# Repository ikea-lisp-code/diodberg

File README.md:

# diodberg

diodberg runs new experimental climbing wall from 'ikea-lisp-code.

The python diodberg module is currently **DEPRECATED**. Development on the wall
client software has moved to a fork of [Firemix]
(https://github.com/ikea-lisp-code/firemix).

If you are currently working on the wall, I recommend just checking out the
repository directly and using classes through the directory hierarchy instead
of using the setup.py file.

Directory/package contents in python/diodberg/:
* core

  Basic types, runner, and rendering objects. User applications interact with
  the wall by directly manipulating pixels on a Panel through an iterator
  interface. This is a strong candidate for future performance improvements.

* data 
  
  Sample configuration files. 

* input
  
  Nothing here! Currently, we lack both software and hardware support for
  sensor input to the wall while in-flight.

* user_plugins

  User applications for running visualizations. If you are writing an
  application to run on the wall, check out things here.

* renderers

  Simulation, serial, and GPIO interfaces for driving lights.

* util

  Misc.: random utilities

* web
  
  A Flask-based web front-end for configuring, controlling, and running lights.

...and: 
* docs
* firmware

  Device firmware for DMX intermediaries

* schematics

# Package requirements
* Python 2.7 
* numpy/scipy
* If simulating plugins: Pygame
* If running serial protocols: pyserial and RPi
* If running the web front end: Flask.
* If using performance optimizations: Numba (and by extension, the Anaconda
  Python distribution). 
* If using audio input: aubio (and its many dependencies).

# Installation and setup instructions
  
  TODO (see above)

# Questions? 

Email <mookerji@spin-one.org>, <chris@notspelledright.com>, <yuanyu.chen@gmail.com>

# License

Copyright (C) 2013 ikea-lisp-code. Distributed under the MIT License.

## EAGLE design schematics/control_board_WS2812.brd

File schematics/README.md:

# diodberg schematics

diodberg schematics require Eagle v6.3.0 or later

...filenames will be cleaned up soon...

# Questions? 

Email <chris@notspelledright.com>, <yuanyu.chen@gmail.com>

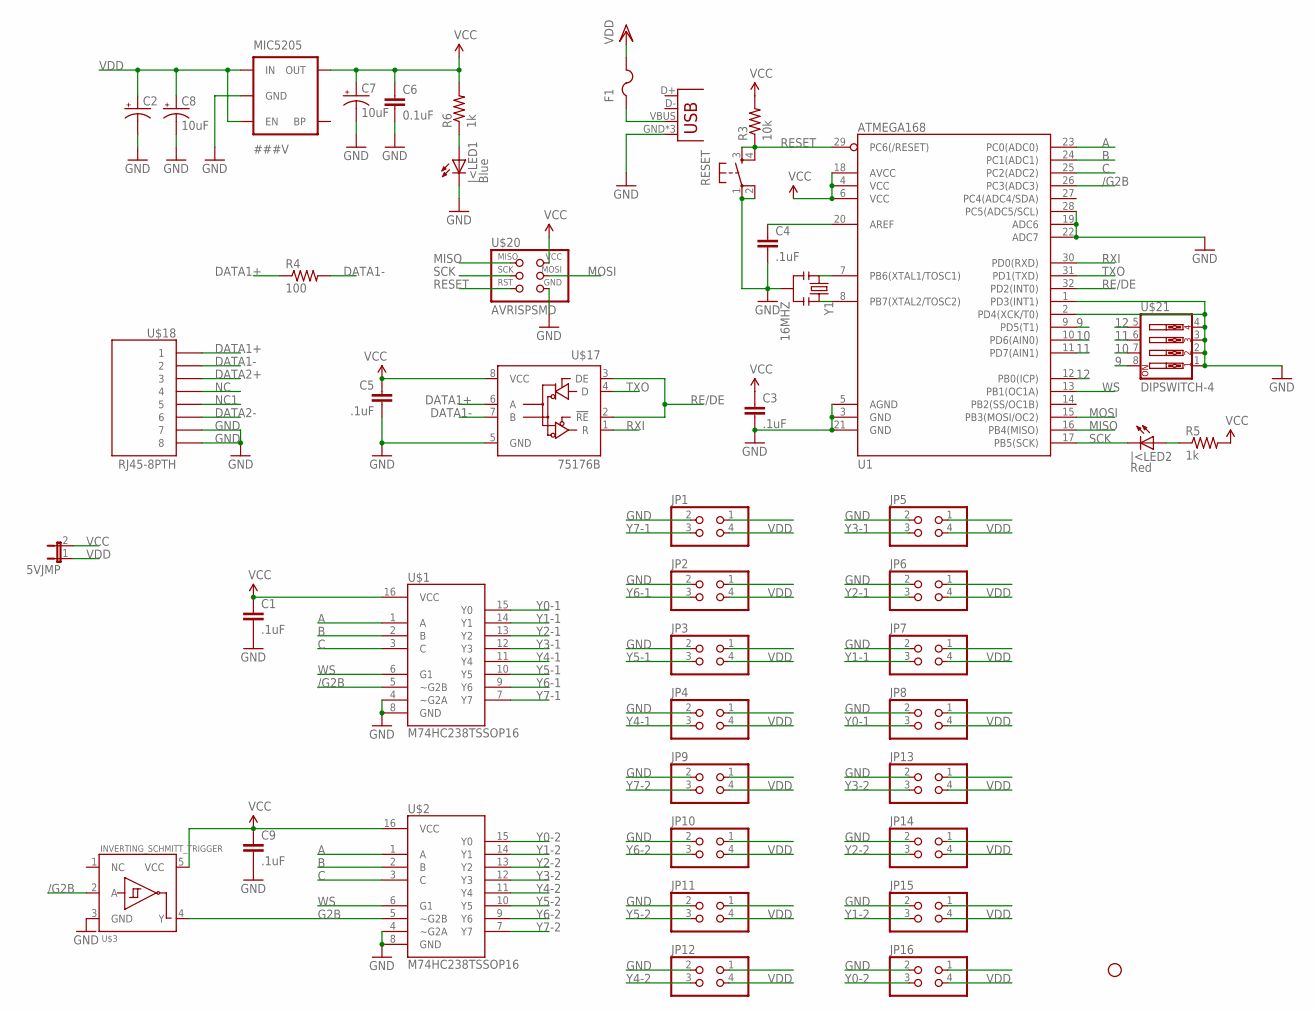
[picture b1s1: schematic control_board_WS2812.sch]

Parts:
5VJMP: JUMPER-2SMD-NO; SJ_2S-NO
C1, C3, C4, C5, C9: .1uF; 0402-CAP
C2: CAP_POLC; PANASONIC_C
C6: 0.1uF; 0402-CAP
C7, C8: 10uF; EIA3216
F1: PTCFUSE-1812; 1812
JP1, JP2, JP3, JP4, JP5, JP6, JP7, JP8, JP9, JP10, JP11, JP12, JP13, JP14, JP15, JP16: PINHD-2X2; 2X02
JP17: USB-MICROB
MIC5205: ###V; SOT23-5
R3: 10k; 0402-RES
R4: 100; 1206
R5, R6: 1k; C0402
RESET: TAC_SWITCHSMD; TACTILE_SWITCH_SMD
STANDOFF1: STAND-OFF
U1: ATMEGA168; TQFP32-08
U$1, U$2: M74HC238TSSOP16; TSSOP16
U$3: INVERTING_SCHMITT_TRIGGER; TSSOP5
U$17: 75176B; D_R-PDSO-G8
U$18: RJ45-8PTH; RJ45-8
U$20: AVRISPSMD; 2X03SMD
U$21: DIPSWITCH-4; DIPSWITCH-04
Y1: 16MHZ; RESONATOR-SMD
|<LED1: Blue; LED-0603
|<LED2: Red; LED-0603

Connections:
9: U1.9 (PD5(T1)), U$21.8
10: U1.10 (PD6(AIN0)), U$21.7
11: U1.11 (PD7(AIN1)), U$21.6
12: U1.12 (PB0(ICP)), U$21.5
/G2B: U1.26 (PC3(ADC3)), U$1.5 (~G2B), U$3.2 (A)
A: U1.23 (PC0(ADC0)), U$1.1 (A), U$2.1 (A)
B: U1.24 (PC1(ADC1)), U$1.2 (B), U$2.2 (B)
C: U1.25 (PC2(ADC2)), U$1.3 (C), U$2.3 (C)
DATA1+: R4.1, U$17.6 (A), U$18.1
DATA1-: R4.2, U$17.7 (B), U$18.2
DATA2+: U$18.3
DATA2-: U$18.6
G2B: U$2.5 (~G2B), U$3.4 (Y)
GND: C1.2, C2.-, C3.2, C4.2, C5.2, C6.2, C7.C (-), C8.C (-), C9.2, JP1.2, JP2.2, JP3.2, JP4.2, JP5.2, JP6.2, JP7.2, JP8.2, JP9.2, JP10.2, JP11.2, JP12.2, JP13.2, JP14.2, JP15.2, JP16.2, JP17.GND, JP17.MT1 (GND), JP17.MT2 (GND), MIC5205.2 (GND), RESET.1, RESET.2, U1.1 (PD3(INT1)), U1.2 (PD4(XCK/T0)), U1.3 (GND), U1.5 (AGND), U1.19 (ADC6), U1.21 (GND), U1.22 (ADC7), U1.28 (PC5(ADC5/SCL)), U$1.4 (~G2A), U$1.8 (GND), U$2.4 (~G2A), U$2.8 (GND), U$3.3 (GND), U$17.5 (GND), U$18.7, U$18.8, U$20.6 (GND), U$21.1, U$21.2, U$21.3, U$21.4, Y1.2, |<LED1.C
MISO: U1.16 (PB4(MISO)), U$20.1 (MISO)
MOSI: U1.15 (PB3(MOSI/OC2)), U$20.4 (MOSI)
unnamed: C4.1, U1.20 (AREF)
unnamed: U1.7 (PB6(XTAL1/TOSC1)), Y1.1
unnamed: U1.8 (PB7(XTAL2/TOSC2)), Y1.3
unnamed: R5.1, |<LED2.A
unnamed: F1.1, JP17.VBUS
unnamed: R6.1, |<LED1.A
NC: U$18.4
NC1: U$18.5
RE/DE: U1.32 (PD2(INT0)), U$17.2 (!RE), U$17.3 (DE)
RESET: R3.1, RESET.3, RESET.4, U1.29 (PC6(/RESET)), U$20.5 (RST)
RXI: U1.30 (PD0(RXD)), U$17.1 (R)
SCK: U1.17 (PB5(SCK)), U$20.3 (SCK), |<LED2.C
TXO: U1.31 (PD1(TXD)), U$17.4 (D)
VCC: 5VJMP.2, C1.1, C3.1, C5.1, C6.1, C7.A (+), C9.1, MIC5205.5 (OUT), R3.2, R5.2, R6.2, U1.4 (VCC), U1.6 (VCC), U1.18 (AVCC), U$1.16 (VCC), U$2.16 (VCC), U$3.5 (VCC), U$17.8 (VCC), U$20.2 (VCC)
VDD: 5VJMP.1, C2.+, C8.A (+), F1.2, JP1.4, JP2.4, JP3.4, JP4.4, JP5.4, JP6.4, JP7.4, JP8.4, JP9.4, JP10.4, JP11.4, JP12.4, JP13.4, JP14.4, JP15.4, JP16.4, MIC5205.1 (IN), MIC5205.3 (EN)
WS: U1.13 (PB1(OC1A)), U$1.6 (G1), U$2.6 (G1)
Y0-1: JP8.3, U$1.15 (Y0)
Y0-2: JP16.3, U$2.15 (Y0)
Y1-1: JP7.3, U$1.14 (Y1)
Y1-2: JP15.3, U$2.14 (Y1)
Y2-1: JP6.3, U$1.13 (Y2)
Y2-2: JP14.3, U$2.13 (Y2)
Y3-1: JP5.3, U$1.12 (Y3)
Y3-2: JP13.3, U$2.12 (Y3)
Y4-1: JP4.3, U$1.11 (Y4)
Y4-2: JP12.3, U$2.11 (Y4)
Y5-1: JP3.3, U$1.10 (Y5)
Y5-2: JP11.3, U$2.10 (Y5)
Y6-1: JP2.3, U$1.9 (Y6)
Y6-2: JP10.3, U$2.9 (Y6)
Y7-1: JP1.3, U$1.7 (Y7)
Y7-2: JP9.3, U$2.7 (Y7)

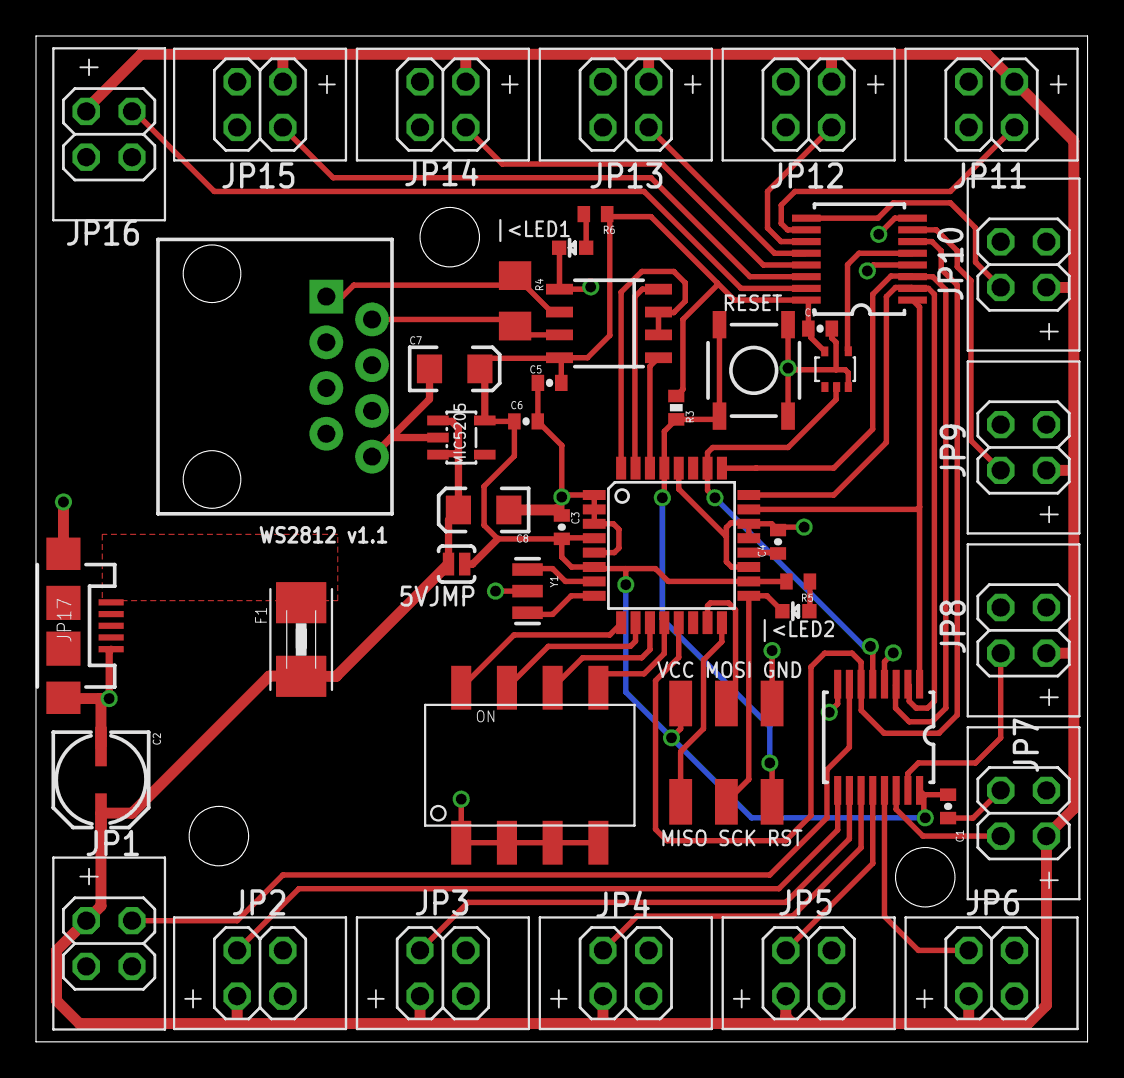
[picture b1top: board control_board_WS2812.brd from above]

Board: 2 copper layers, 58.4 x 55.9 mm, 48 parts (0 on the bottom side), 44 nets.

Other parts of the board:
STANDOFF2, STANDOFF3: STAND-OFF

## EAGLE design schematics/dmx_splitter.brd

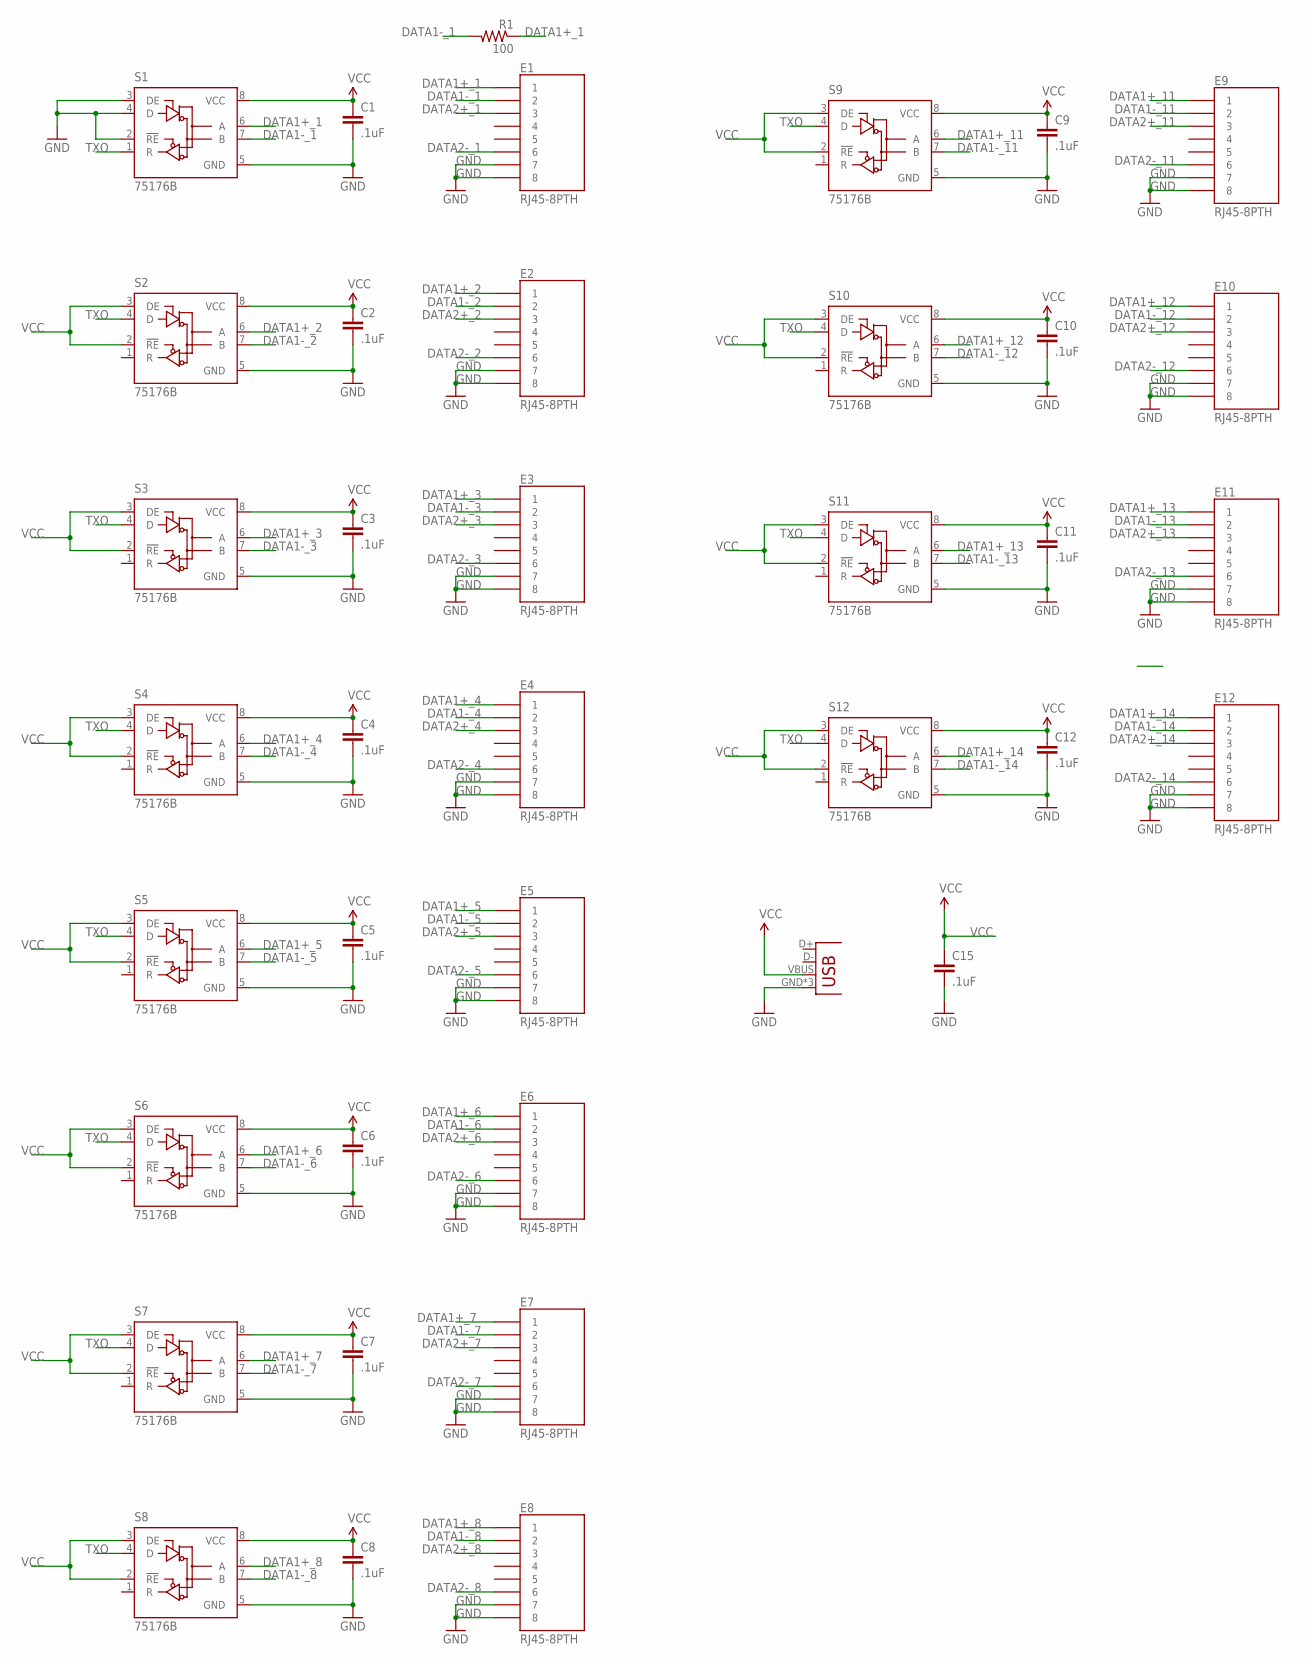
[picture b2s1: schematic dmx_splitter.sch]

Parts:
C1, C2, C3, C4, C5, C6, C7, C8, C9, C10, C11, C12, C15: .1uF; 0402-CAP
E1, E2, E3, E4, E5, E6, E7, E8, E9, E10, E11, E12: RJ45-8PTH; RJ45-8
JP1: USB-MICROB
R1: 100; 1206
S1, S2, S3, S4, S5, S6, S7, S8, S9, S10, S11, S12: 75176B; D_R-PDSO-G8

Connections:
DATA1+_1: E1.1, R1.1, S1.6 (A)
DATA1+_2: E2.1, S2.6 (A)
DATA1+_3: E3.1, S3.6 (A)
DATA1+_4: E4.1, S4.6 (A)
DATA1+_5: E5.1, S5.6 (A)
DATA1+_6: E6.1, S6.6 (A)
DATA1+_7: E7.1, S7.6 (A)
DATA1+_8: E8.1, S8.6 (A)
DATA1+_11: E9.1, S9.6 (A)
DATA1+_12: E10.1, S10.6 (A)
DATA1+_13: E11.1, S11.6 (A)
DATA1+_14: E12.1, S12.6 (A)
DATA1-_1: E1.2, R1.2, S1.7 (B)
DATA1-_2: E2.2, S2.7 (B)
DATA1-_3: E3.2, S3.7 (B)
DATA1-_4: E4.2, S4.7 (B)
DATA1-_5: E5.2, S5.7 (B)
DATA1-_6: E6.2, S6.7 (B)
DATA1-_7: E7.2, S7.7 (B)
DATA1-_8: E8.2, S8.7 (B)
DATA1-_11: E9.2, S9.7 (B)
DATA1-_12: E10.2, S10.7 (B)
DATA1-_13: E11.2, S11.7 (B)
DATA1-_14: E12.2, S12.7 (B)
DATA2+_1: E1.3
DATA2+_2: E2.3
DATA2+_3: E3.3
DATA2+_4: E4.3
DATA2+_5: E5.3
DATA2+_6: E6.3
DATA2+_7: E7.3
DATA2+_8: E8.3
DATA2+_11: E9.3
DATA2+_12: E10.3
DATA2+_13: E11.3
DATA2+_14: E12.3
DATA2-_1: E1.6
DATA2-_2: E2.6
DATA2-_3: E3.6
DATA2-_4: E4.6
DATA2-_5: E5.6
DATA2-_6: E6.6
DATA2-_7: E7.6
DATA2-_8: E8.6
DATA2-_11: E9.6
DATA2-_12: E10.6
DATA2-_13: E11.6
DATA2-_14: E12.6
GND: C1.2, C2.2, C3.2, C4.2, C5.2, C6.2, C7.2, C8.2, C9.2, C10.2, C11.2, C12.2, C15.2, E1.7, E1.8, E2.7, E2.8, E3.7, E3.8, E4.7, E4.8, E5.7, E5.8, E6.7, E6.8, E7.7, E7.8, E8.7, E8.8, E9.7, E9.8, E10.7, E10.8, E11.7, E11.8, E12.7, E12.8, JP1.GND, JP1.MT1 (GND), JP1.MT2 (GND), S1.2 (!RE), S1.3 (DE), S1.4 (D), S1.5 (GND), S2.5 (GND), S3.5 (GND), S4.5 (GND), S5.5 (GND), S6.5 (GND), S7.5 (GND), S8.5 (GND), S9.5 (GND), S10.5 (GND), S11.5 (GND), S12.5 (GND)
TXO: S1.1 (R), S2.4 (D), S3.4 (D), S4.4 (D), S5.4 (D), S6.4 (D), S7.4 (D), S8.4 (D), S9.4 (D), S10.4 (D), S11.4 (D), S12.4 (D)
VCC: C1.1, C2.1, C3.1, C4.1, C5.1, C6.1, C7.1, C8.1, C9.1, C10.1, C11.1, C12.1, C15.1, JP1.VBUS, S1.8 (VCC), S2.2 (!RE), S2.3 (DE), S2.8 (VCC), S3.2 (!RE), S3.3 (DE), S3.8 (VCC), S4.2 (!RE), S4.3 (DE), S4.8 (VCC), S5.2 (!RE), S5.3 (DE), S5.8 (VCC), S6.2 (!RE), S6.3 (DE), S6.8 (VCC), S7.2 (!RE), S7.3 (DE), S7.8 (VCC), S8.2 (!RE), S8.3 (DE), S8.8 (VCC), S9.2 (!RE), S9.3 (DE), S9.8 (VCC), S10.2 (!RE), S10.3 (DE), S10.8 (VCC), S11.2 (!RE), S11.3 (DE), S11.8 (VCC), S12.2 (!RE), S12.3 (DE), S12.8 (VCC)

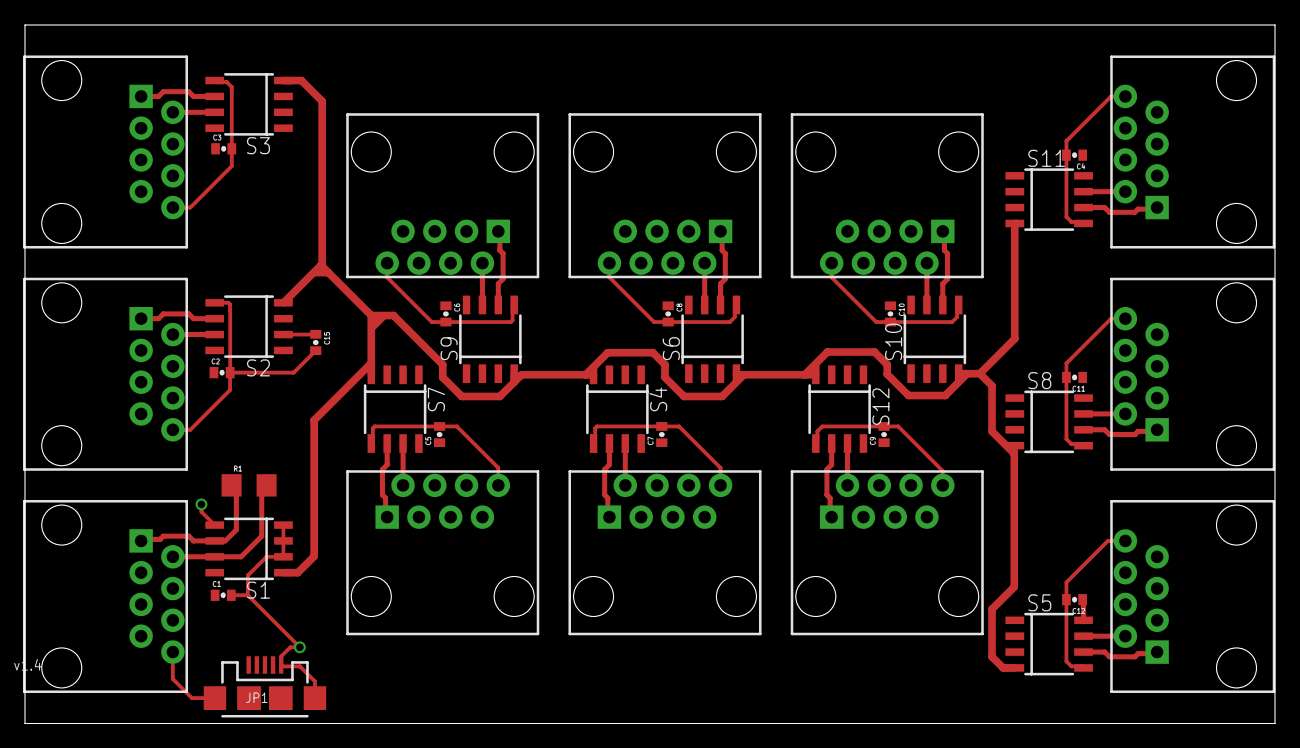
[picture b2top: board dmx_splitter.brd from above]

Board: 2 copper layers, 100.0 x 55.9 mm, 39 parts (0 on the bottom side), 27 nets.

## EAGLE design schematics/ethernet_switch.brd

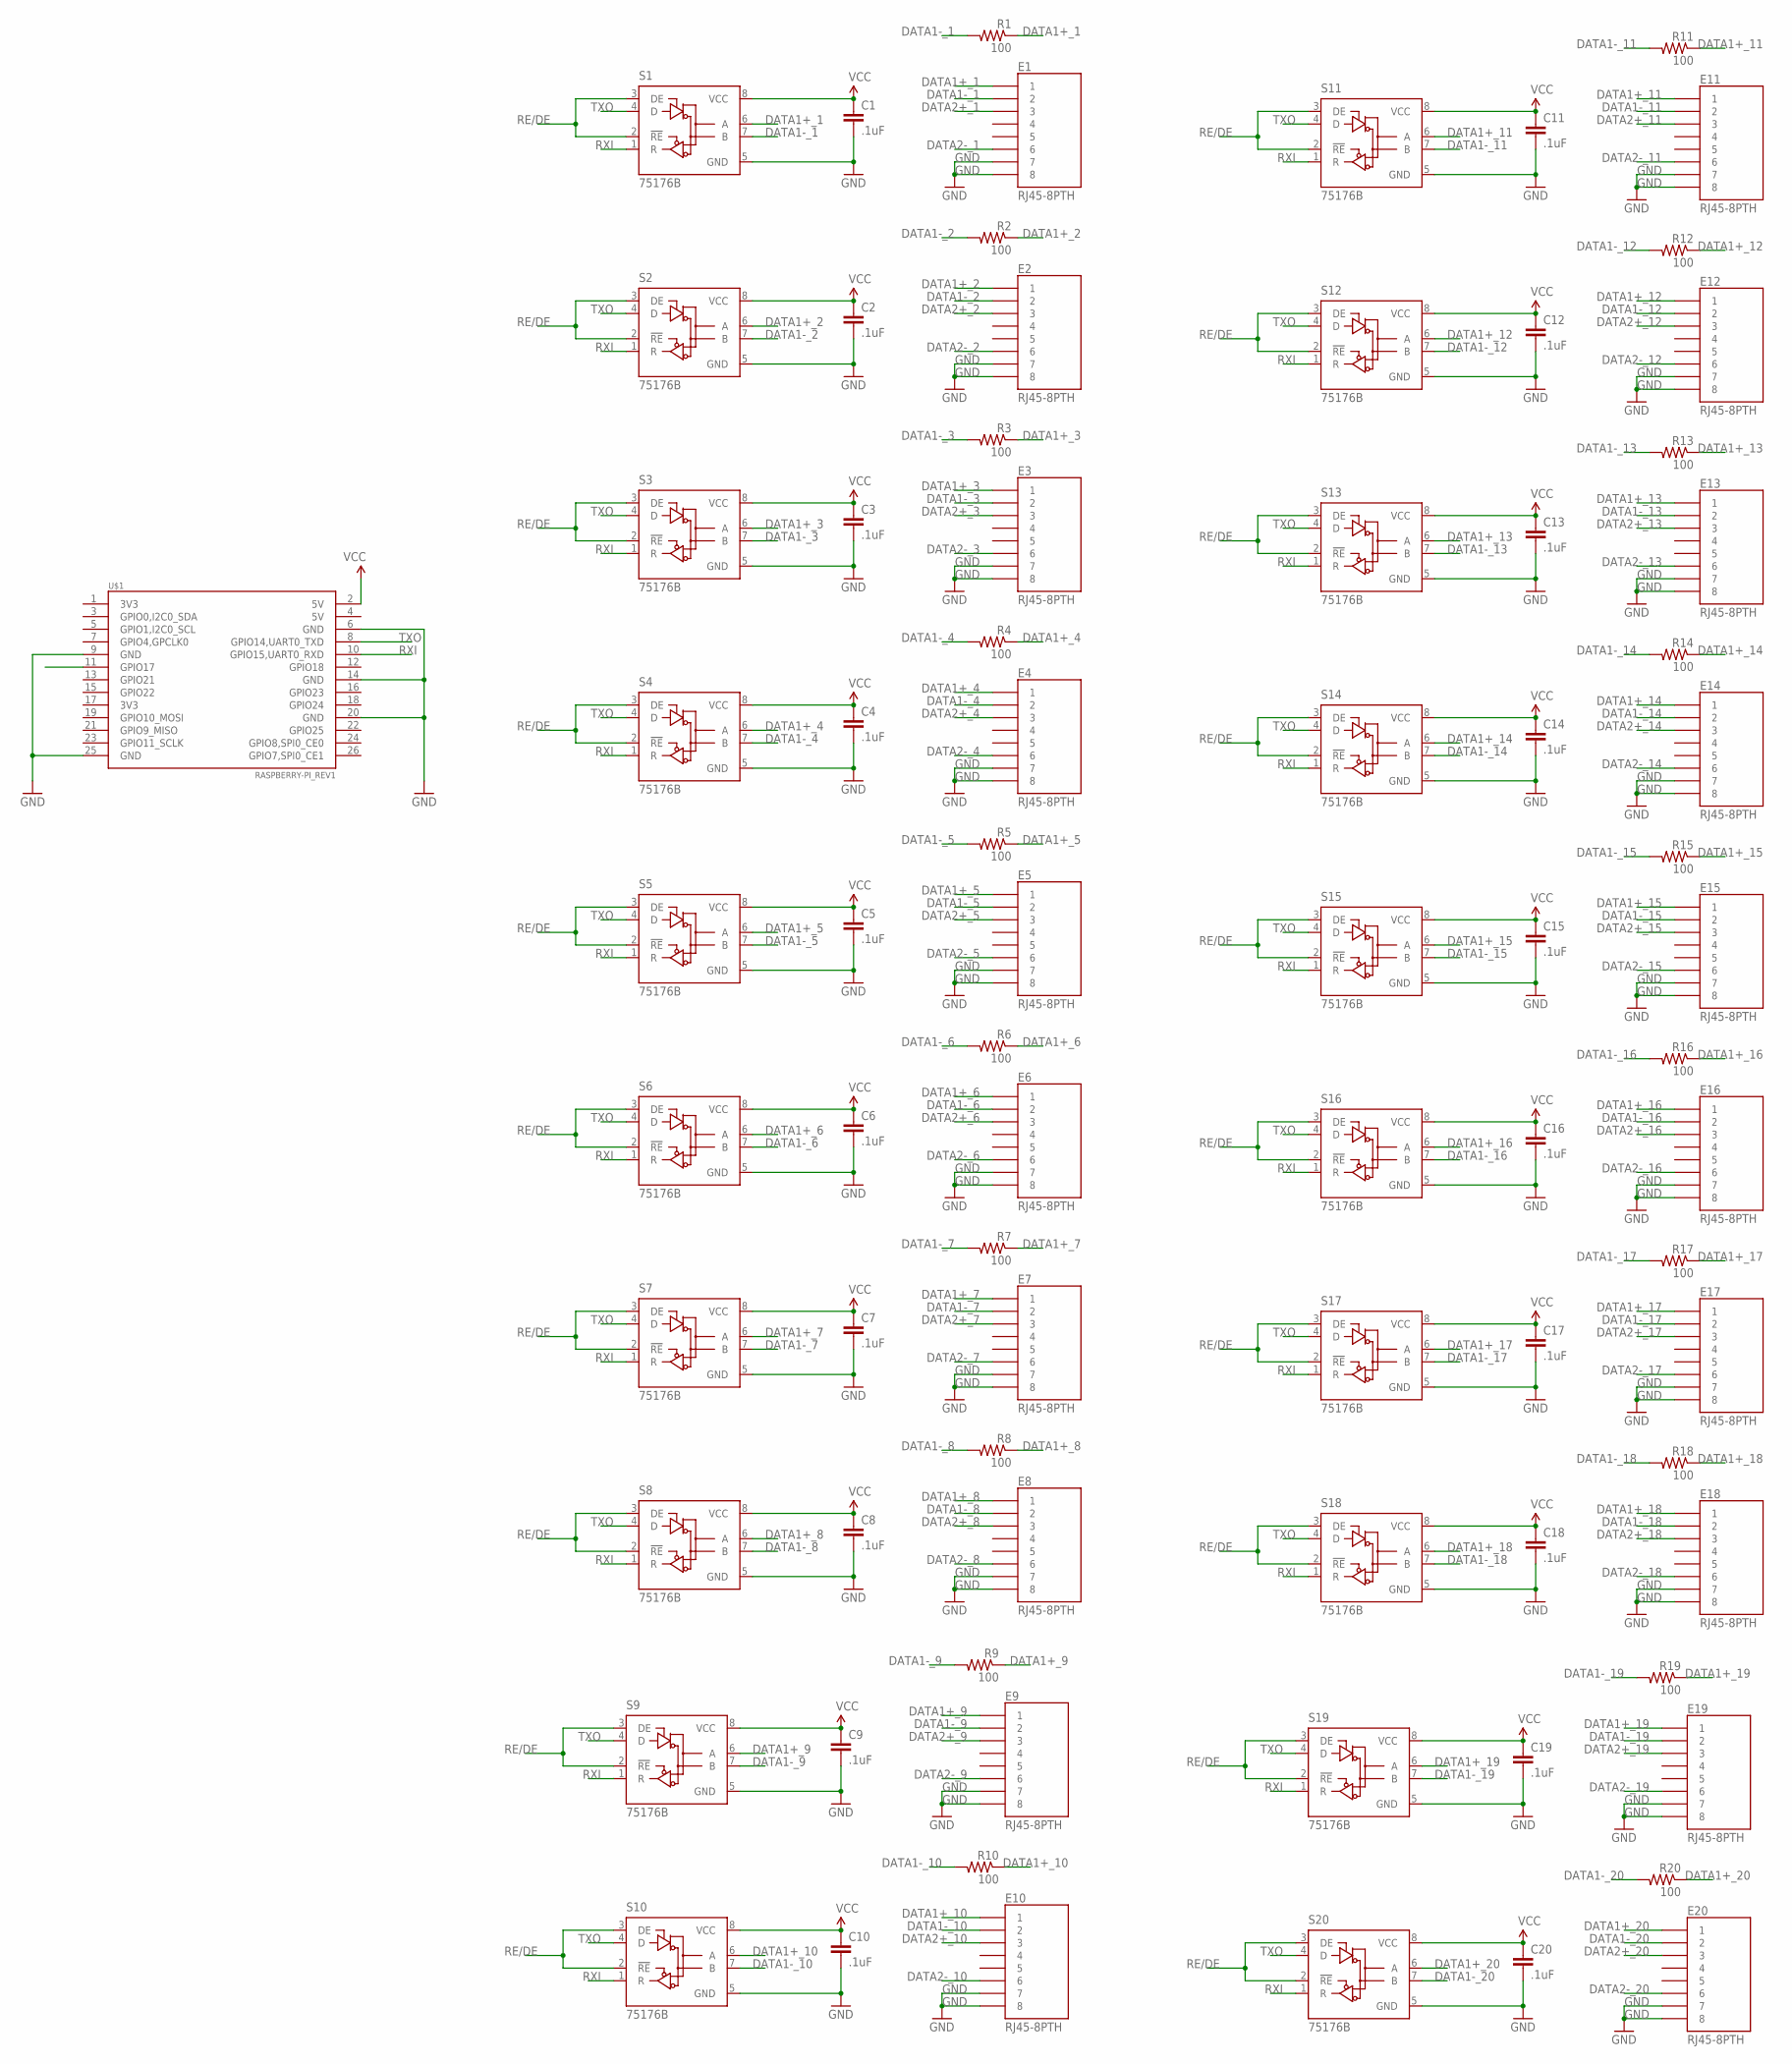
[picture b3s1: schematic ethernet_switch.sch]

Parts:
C1, C2, C3, C4, C5, C6, C7, C8, C9, C10, C11, C12, C13, C14, C15, C16, C17, C18, C19, C20: .1uF; 0402-CAP
E1, E2, E3, E4, E5, E6, E7, E8, E9, E10, E11, E12, E13, E14, E15, E16, E17, E18, E19, E20: RJ45-8PTH; RJ45-8
R1, R2, R3, R4, R5, R6, R7, R8, R9, R10, R11, R12, R13, R14, R15, R16, R17, R18, R19, R20: 100; 1206
S1, S2, S3, S4, S5, S6, S7, S8, S9, S10, S11, S12, S13, S14, S15, S16, S17, S18, S19, S20: 75176B; D_R-PDSO-G8
U$1: RASPBERRY-PI_REV1

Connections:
DATA1+_1: E1.1, R1.1, S1.6 (A)
DATA1+_2: E2.1, R2.1, S2.6 (A)
DATA1+_3: E3.1, R3.1, S3.6 (A)
DATA1+_4: E4.1, R4.1, S4.6 (A)
DATA1+_5: E5.1, R5.1, S5.6 (A)
DATA1+_6: E6.1, R6.1, S6.6 (A)
DATA1+_7: E7.1, R7.1, S7.6 (A)
DATA1+_8: E8.1, R8.1, S8.6 (A)
DATA1+_9: E9.1, R9.1, S9.6 (A)
DATA1+_10: E10.1, R10.1, S10.6 (A)
DATA1+_11: E11.1, R11.1, S11.6 (A)
DATA1+_12: E12.1, R12.1, S12.6 (A)
DATA1+_13: E13.1, R13.1, S13.6 (A)
DATA1+_14: E14.1, R14.1, S14.6 (A)
DATA1+_15: E15.1, R15.1, S15.6 (A)
DATA1+_16: E16.1, R16.1, S16.6 (A)
DATA1+_17: E17.1, R17.1, S17.6 (A)
DATA1+_18: E18.1, R18.1, S18.6 (A)
DATA1+_19: E19.1, R19.1, S19.6 (A)
DATA1+_20: E20.1, R20.1, S20.6 (A)
DATA1-_1: E1.2, R1.2, S1.7 (B)
DATA1-_2: E2.2, R2.2, S2.7 (B)
DATA1-_3: E3.2, R3.2, S3.7 (B)
DATA1-_4: E4.2, R4.2, S4.7 (B)
DATA1-_5: E5.2, R5.2, S5.7 (B)
DATA1-_6: E6.2, R6.2, S6.7 (B)
DATA1-_7: E7.2, R7.2, S7.7 (B)
DATA1-_8: E8.2, R8.2, S8.7 (B)
DATA1-_9: E9.2, R9.2, S9.7 (B)
DATA1-_10: E10.2, R10.2, S10.7 (B)
DATA1-_11: E11.2, R11.2, S11.7 (B)
DATA1-_12: E12.2, R12.2, S12.7 (B)
DATA1-_13: E13.2, R13.2, S13.7 (B)
DATA1-_14: E14.2, R14.2, S14.7 (B)
DATA1-_15: E15.2, R15.2, S15.7 (B)
DATA1-_16: E16.2, R16.2, S16.7 (B)
DATA1-_17: E17.2, R17.2, S17.7 (B)
DATA1-_18: E18.2, R18.2, S18.7 (B)
DATA1-_19: E19.2, R19.2, S19.7 (B)
DATA1-_20: E20.2, R20.2, S20.7 (B)
DATA2+_1: E1.3
DATA2+_2: E2.3
DATA2+_3: E3.3
DATA2+_4: E4.3
DATA2+_5: E5.3
DATA2+_6: E6.3
DATA2+_7: E7.3
DATA2+_8: E8.3
DATA2+_9: E9.3
DATA2+_10: E10.3
DATA2+_11: E11.3
DATA2+_12: E12.3
DATA2+_13: E13.3
DATA2+_14: E14.3
DATA2+_15: E15.3
DATA2+_16: E16.3
DATA2+_17: E17.3
DATA2+_18: E18.3
DATA2+_19: E19.3
DATA2+_20: E20.3
DATA2-_1: E1.6
DATA2-_2: E2.6
DATA2-_3: E3.6
DATA2-_4: E4.6
DATA2-_5: E5.6
DATA2-_6: E6.6
DATA2-_7: E7.6
DATA2-_8: E8.6
DATA2-_9: E9.6
DATA2-_10: E10.6
DATA2-_11: E11.6
DATA2-_12: E12.6
DATA2-_13: E13.6
DATA2-_14: E14.6
DATA2-_15: E15.6
DATA2-_16: E16.6
DATA2-_17: E17.6
DATA2-_18: E18.6
DATA2-_19: E19.6
DATA2-_20: E20.6
GND: C1.2, C2.2, C3.2, C4.2, C5.2, C6.2, C7.2, C8.2, C9.2, C10.2, C11.2, C12.2, C13.2, C14.2, C15.2, C16.2, C17.2, C18.2, C19.2, C20.2, E1.7, E1.8, E2.7, E2.8, E3.7, E3.8, E4.7, E4.8, E5.7, E5.8, E6.7, E6.8, E7.7, E7.8, E8.7, E8.8, E9.7, E9.8, E10.7, E10.8, E11.7, E11.8, E12.7, E12.8, E13.7, E13.8, E14.7, E14.8, E15.7, E15.8, E16.7, E16.8, E17.7, E17.8, E18.7, E18.8, E19.7, E19.8, E20.7, E20.8, S1.5 (GND), S2.5 (GND), S3.5 (GND), S4.5 (GND), S5.5 (GND), S6.5 (GND), S7.5 (GND), S8.5 (GND), S9.5 (GND), S10.5 (GND), S11.5 (GND), S12.5 (GND), S13.5 (GND), S14.5 (GND), S15.5 (GND), S16.5 (GND), S17.5 (GND), S18.5 (GND), S19.5 (GND), S20.5 (GND), U$1.6 (GND), U$1.9 (GND), U$1.14 (GND), U$1.20 (GND), U$1.25 (GND)
RE/DE: S1.2 (!RE), S1.3 (DE), S2.2 (!RE), S2.3 (DE), S3.2 (!RE), S3.3 (DE), S4.2 (!RE), S4.3 (DE), S5.2 (!RE), S5.3 (DE), S6.2 (!RE), S6.3 (DE), S7.2 (!RE), S7.3 (DE), S8.2 (!RE), S8.3 (DE), S9.2 (!RE), S9.3 (DE), S10.2 (!RE), S10.3 (DE), S11.2 (!RE), S11.3 (DE), S12.2 (!RE), S12.3 (DE), S13.2 (!RE), S13.3 (DE), S14.2 (!RE), S14.3 (DE), S15.2 (!RE), S15.3 (DE), S16.2 (!RE), S16.3 (DE), S17.2 (!RE), S17.3 (DE), S18.2 (!RE), S18.3 (DE), S19.2 (!RE), S19.3 (DE), S20.2 (!RE), S20.3 (DE), U$1.11 (GPIO17)
RXI: S1.1 (R), S2.1 (R), S3.1 (R), S4.1 (R), S5.1 (R), S6.1 (R), S7.1 (R), S8.1 (R), S9.1 (R), S10.1 (R), S11.1 (R), S12.1 (R), S13.1 (R), S14.1 (R), S15.1 (R), S16.1 (R), S17.1 (R), S18.1 (R), S19.1 (R), S20.1 (R), U$1.10 (GPIO15,UART0_RXD)
TXO: S1.4 (D), S2.4 (D), S3.4 (D), S4.4 (D), S5.4 (D), S6.4 (D), S7.4 (D), S8.4 (D), S9.4 (D), S10.4 (D), S11.4 (D), S12.4 (D), S13.4 (D), S14.4 (D), S15.4 (D), S16.4 (D), S17.4 (D), S18.4 (D), S19.4 (D), S20.4 (D), U$1.8 (GPIO14,UART0_TXD)
VCC: C1.1, C2.1, C3.1, C4.1, C5.1, C6.1, C7.1, C8.1, C9.1, C10.1, C11.1, C12.1, C13.1, C14.1, C15.1, C16.1, C17.1, C18.1, C19.1, C20.1, S1.8 (VCC), S2.8 (VCC), S3.8 (VCC), S4.8 (VCC), S5.8 (VCC), S6.8 (VCC), S7.8 (VCC), S8.8 (VCC), S9.8 (VCC), S10.8 (VCC), S11.8 (VCC), S12.8 (VCC), S13.8 (VCC), S14.8 (VCC), S15.8 (VCC), S16.8 (VCC), S17.8 (VCC), S18.8 (VCC), S19.8 (VCC), S20.8 (VCC), U$1.2 (5V)

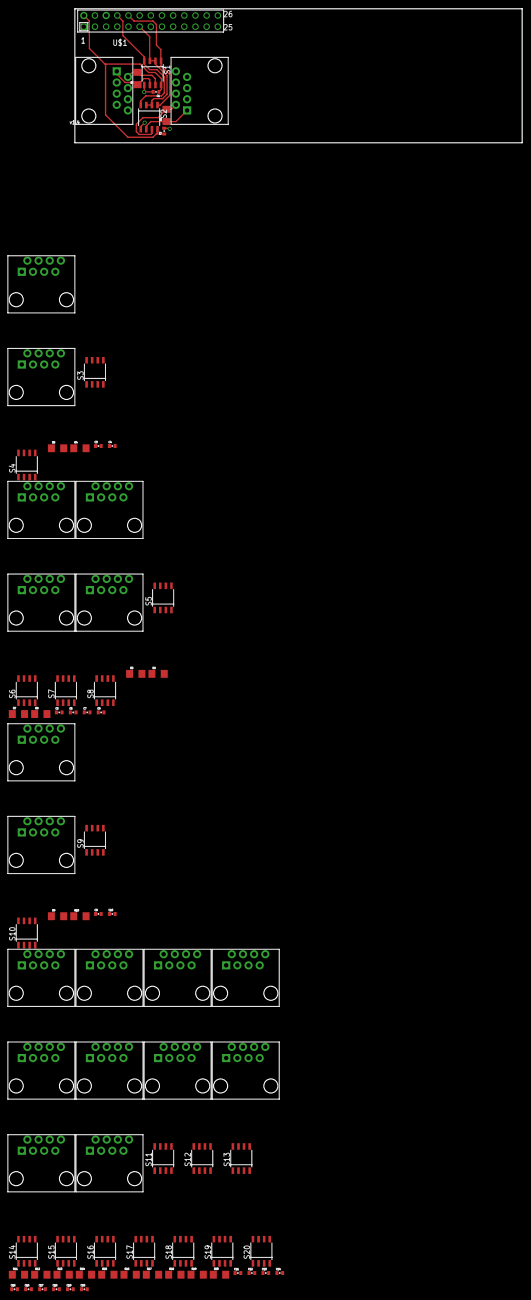
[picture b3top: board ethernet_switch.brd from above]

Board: 2 copper layers, 101.7 x 30.5 mm, 81 parts (0 on the bottom side), 45 nets.

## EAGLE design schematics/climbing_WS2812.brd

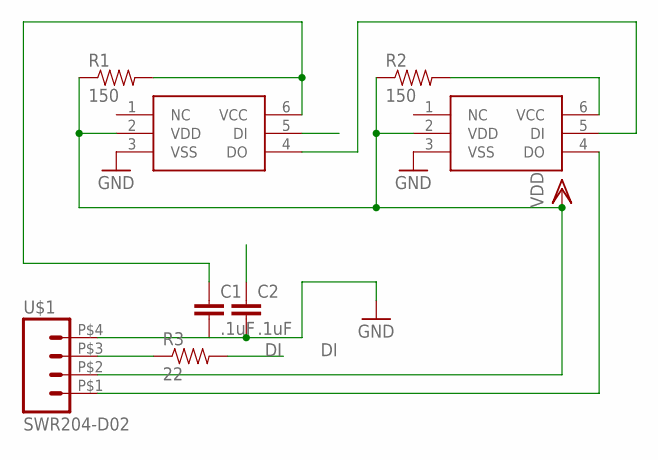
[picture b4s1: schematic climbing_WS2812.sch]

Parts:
C1, C2: .1uF; 0603-CAP
R1, R2: 150; 0603-RES
R3: 22; 0603-RES
U$1: SWR204-D02; SWR204
U$2, U$3: WS2812; RGBLED5050

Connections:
DI: R3.2, U$2.5 (DI)
DODI: U$2.4 (DO), U$3.5 (DI)
GND: C1.2, C2.2, U$1.P$4 (4), U$2.3 (VSS), U$3.3 (VSS)
unnamed: R3.1, U$1.P$3 (3)
unnamed: U$1.P$1 (1), U$3.4 (DO)
VCC: C1.1, R1.2, U$2.6 (VCC)
VCC2: C2.1, R2.2, U$3.6 (VCC)
VDD: R1.1, R2.1, U$1.P$2 (2), U$2.2 (VDD), U$3.2 (VDD)

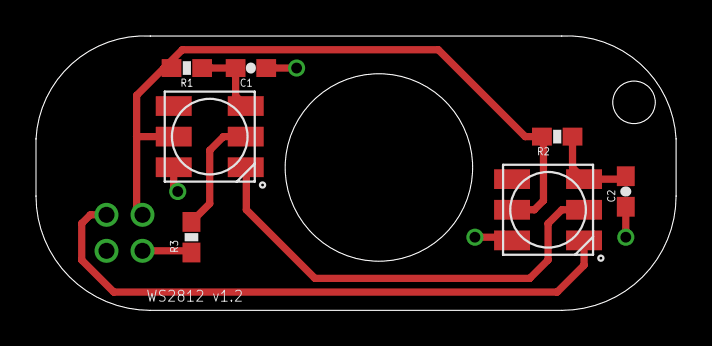
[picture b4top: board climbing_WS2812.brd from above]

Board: 2 copper layers, 35.6 x 15.2 mm, 8 parts (1 on the bottom side), 8 nets.

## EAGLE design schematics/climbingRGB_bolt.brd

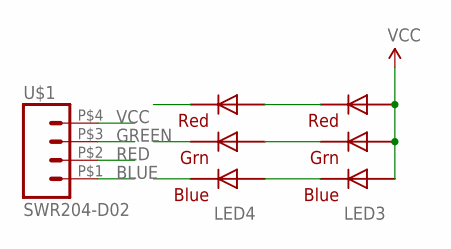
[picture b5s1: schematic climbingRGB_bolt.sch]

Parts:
LED3, LED4: RGBLED5050
U$1: SWR204-D02; SWR204

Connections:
BLUE: LED4.4 (BLUE_C), U$1.P$1 (1)
GREEN: LED4.6 (GREEN_C), U$1.P$3 (3)
unnamed: LED3.4 (BLUE_C), LED4.3 (BLUE_A)
unnamed: LED3.6 (GREEN_C), LED4.1 (GREEN_A)
unnamed: LED3.5 (RED_C), LED4.2 (RED_A)
RED: LED4.5 (RED_C), U$1.P$2 (2)
VCC: LED3.1 (GREEN_A), LED3.2 (RED_A), LED3.3 (BLUE_A), U$1.P$4 (4)

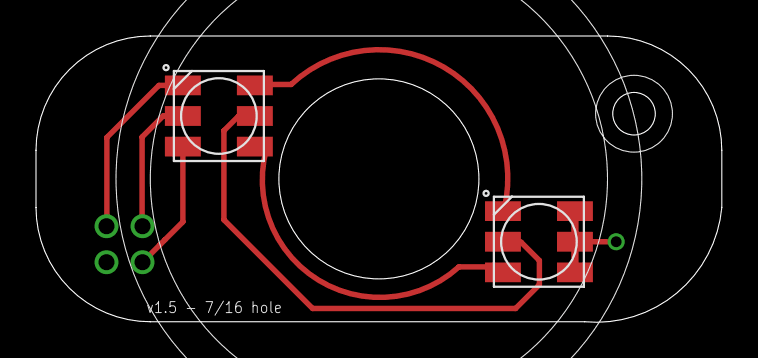
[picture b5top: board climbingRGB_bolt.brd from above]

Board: 2 copper layers, 38.1 x 15.9 mm, 3 parts (1 on the bottom side), 7 nets.

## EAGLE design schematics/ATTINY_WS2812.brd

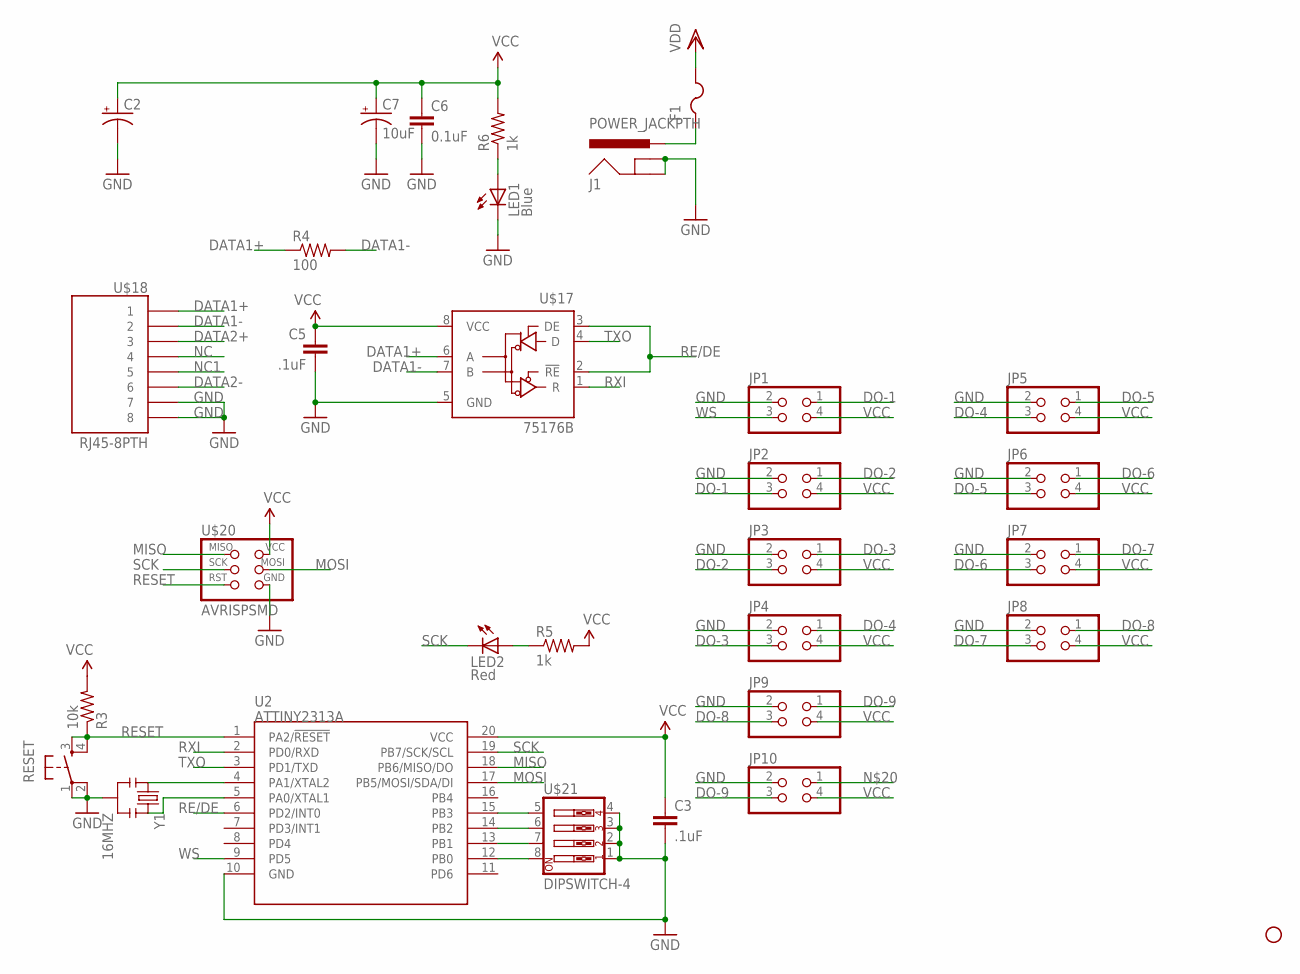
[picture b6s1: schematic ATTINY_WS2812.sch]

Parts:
C2: CAP_POLC; PANASONIC_C
C3, C5: .1uF; 0402-CAP
C6: 0.1uF; 0402-CAP
C7: 10uF; EIA3216
F1: PTCFUSE-1812; 1812
J1: POWER_JACKPTH; POWER_JACK_PTH
JP1, JP2, JP3, JP4, JP5, JP6, JP7, JP8, JP9, JP10: PINHD-2X2; 2X02
LED1: Blue; LED-0603
LED2: Red; LED-0603
R3: 10k; 0402-RES
R4: 100; 1206
R5, R6: 1k; C0402
RESET: TAC_SWITCHSMD; TACTILE_SWITCH_SMD
STANDOFF1: STAND-OFF
U2: ATTINY2313A; SOP20W
U$17: 75176B; D_R-PDSO-G8
U$18: RJ45-8PTH; RJ45-8
U$20: AVRISPSMD; 2X03SMD
U$21: DIPSWITCH-4; DIPSWITCH-04
Y1: 16MHZ; RESONATOR-SMD

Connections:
DATA1+: R4.1, U$17.6 (A), U$18.1
DATA1-: R4.2, U$17.7 (B), U$18.2
DATA2+: U$18.3
DATA2-: U$18.6
DO-1: JP1.1, JP2.3
DO-2: JP2.1, JP3.3
DO-3: JP3.1, JP4.3
DO-4: JP4.1, JP5.3
DO-5: JP5.1, JP6.3
DO-6: JP6.1, JP7.3
DO-7: JP7.1, JP8.3
DO-8: JP8.1, JP9.3
DO-9: JP9.1, JP10.3
GND: C2.-, C3.2, C5.2, C6.2, C7.C (-), J1.GND, J1.GNDBREAK, JP1.2, JP2.2, JP3.2, JP4.2, JP5.2, JP6.2, JP7.2, JP8.2, JP9.2, JP10.2, LED1.C, RESET.1, RESET.2, U2.10 (GND), U$17.5 (GND), U$18.7, U$18.8, U$20.6 (GND), U$21.1, U$21.2, U$21.3, U$21.4, Y1.2
MISO: U2.18 (PB6/MISO/DO), U$20.1 (MISO)
MOSI: U2.17 (PB5/MOSI/SDA/DI), U$20.4 (MOSI)
unnamed: U2.15 (PB3), U$21.5
unnamed: U2.5 (PA0/XTAL1), Y1.3
unnamed: U2.14 (PB2), U$21.6
unnamed: U2.4 (PA1/XTAL2), Y1.1
unnamed: U2.13 (PB1), U$21.7
unnamed: LED2.A, R5.1
unnamed: F1.1, J1.PWR
unnamed: U2.12 (PB0), U$21.8
unnamed: LED1.A, R6.1
NC: U$18.4
NC1: U$18.5
RE/DE: U2.6 (PD2/INT0), U$17.2 (!RE), U$17.3 (DE)
RESET: R3.1, RESET.3, RESET.4, U2.1 (PA2/!RESET), U$20.5 (RST)
RXI: U2.2 (PD0/RXD), U$17.1 (R)
SCK: LED2.C, U2.19 (PB7/SCK/SCL), U$20.3 (SCK)
TXO: U2.3 (PD1/TXD), U$17.4 (D)
VCC: C2.+, C3.1, C5.1, C6.1, C7.A (+), F1.2, JP1.4, JP2.4, JP3.4, JP4.4, JP5.4, JP6.4, JP7.4, JP8.4, JP9.4, JP10.4, R3.2, R5.2, R6.2, U2.20 (VCC), U$17.8 (VCC), U$20.2 (VCC)
WS: JP1.3, U2.9 (PD5)

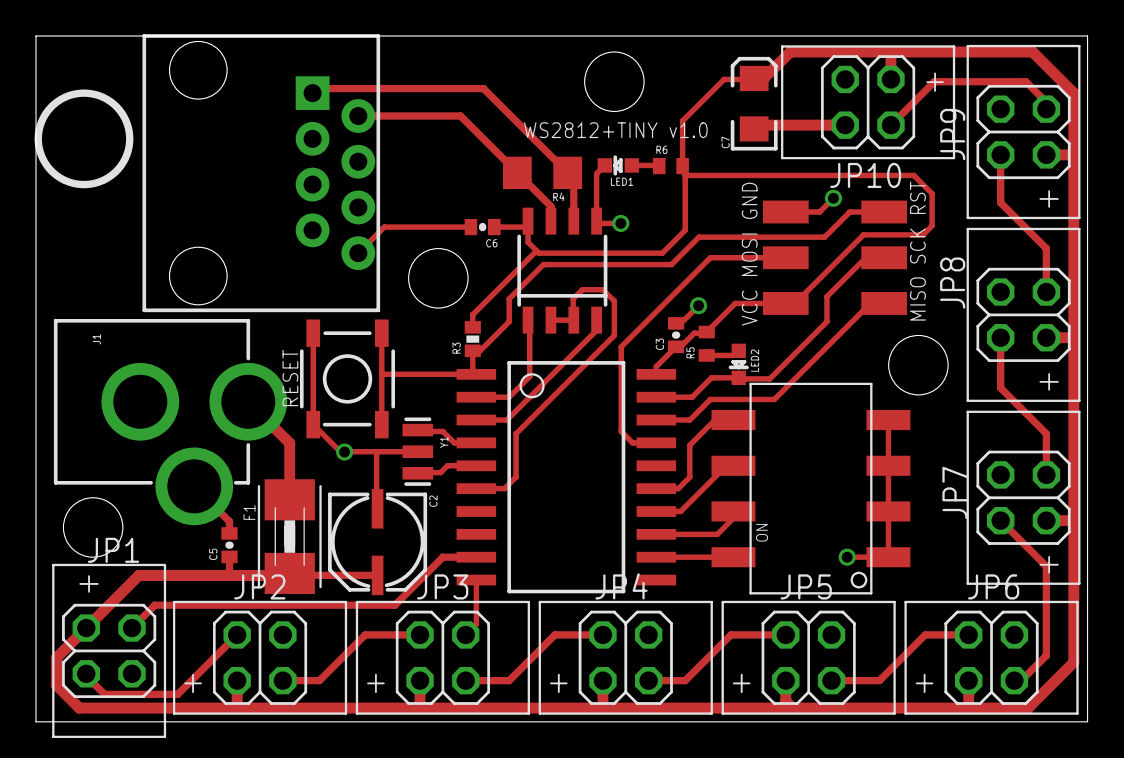
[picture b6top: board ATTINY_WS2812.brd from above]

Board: 2 copper layers, 58.4 x 38.1 mm, 34 parts (0 on the bottom side), 30 nets.

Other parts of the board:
STANDOFF2, STANDOFF3, STANDOFF4: STAND-OFF

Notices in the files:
parts and their libraries:
SparkFun-DigitalIC: Licensing: CC v3.0 Share-Alike You are welcome to use this library for commercial purposes.
